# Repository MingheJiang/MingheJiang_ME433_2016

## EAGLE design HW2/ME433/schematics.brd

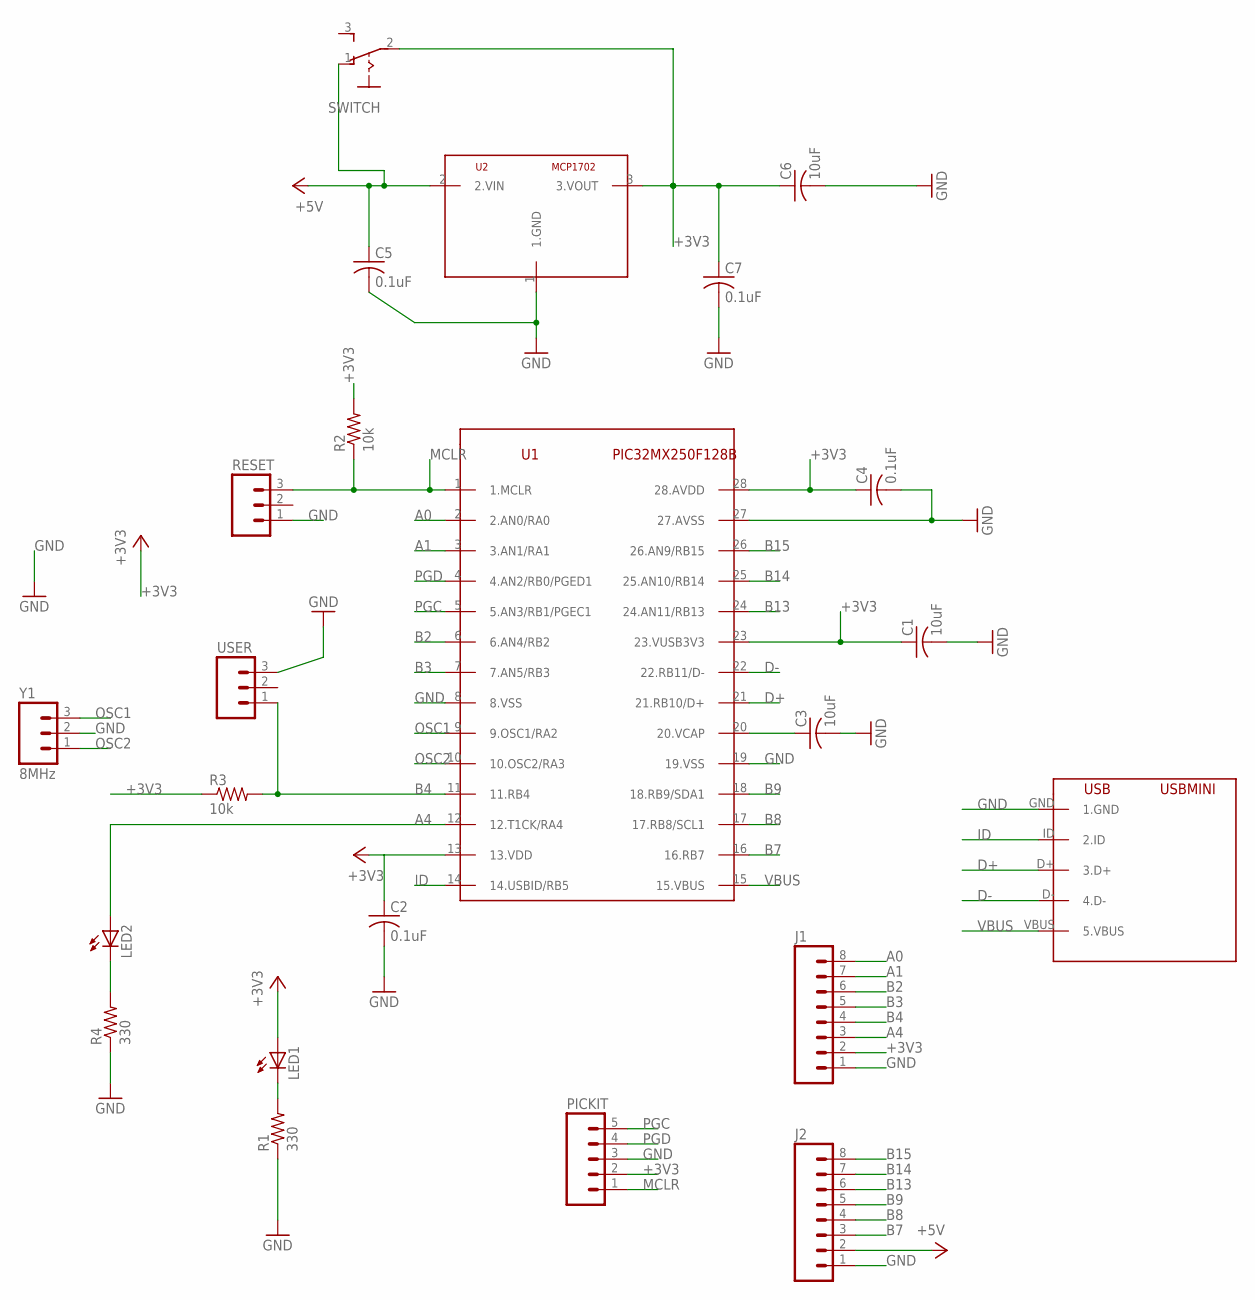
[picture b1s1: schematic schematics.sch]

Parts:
C1, C3, C6: 10uF; C025-024X044
C2, C4, C5, C7: 0.1uF; C025-024X044
J1, J2: M08; 1X08_ROUND
LED1, LED2: LED3MM
PICKIT: M05PTH; 1X05
R1, R4: 330; 0207/10
R2, R3: 10k; 0207/10
RESET: M03PTH; 1X03
SWITCH: 255SB
U1: PIC32MX250F128B; DIL28-3
U2: MCP1702; TO92
USB: USBMINI; USB-MB-H
USER: M03PTH; 1X03
Y1: 8MHz; 1X03

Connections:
+3V3: C1.1, C2.1, C4.1, C6.1, C7.1, J1.2, LED1.A, PICKIT.2, R2.2, R3.1, SWITCH.2, U1.13 (13.VDD), U1.23 (23.VUSB3V3), U1.28 (28.AVDD), U2.3 (3.VOUT)
+5V: C5.1, J2.2, SWITCH.1 (O), U2.2 (2.VIN)
A0: J1.8, U1.2 (2.AN0/RA0)
A1: J1.7, U1.3 (3.AN1/RA1)
A4: J1.3, LED2.A, U1.12 (12.T1CK/RA4)
B2: J1.6, U1.6 (6.AN4/RB2)
B3: J1.5, U1.7 (7.AN5/RB3)
B4: J1.4, R3.2, U1.11 (11.RB4), USER.1
B7: J2.3, U1.16 (16.RB7)
B8: J2.4, U1.17 (17.RB8/SCL1)
B9: J2.5, U1.18 (18.RB9/SDA1)
B13: J2.6, U1.24 (24.AN11/RB13)
B14: J2.7, U1.25 (25.AN10/RB14)
B15: J2.8, U1.26 (26.AN9/RB15)
D+: U1.21 (21.RB10/D+), USB.D+ (3.D+)
D-: U1.22 (22.RB11/D-), USB.D- (4.D-)
GND: C1.2, C2.2, C3.2, C4.2, C5.2, C6.2, C7.2, J1.1, J2.1, PICKIT.3, R1.1, R4.1, RESET.1, U1.8 (8.VSS), U1.19 (19.VSS), U1.27 (27.AVSS), U2.1 (1.GND), USB.GND (1.GND), USER.3, Y1.2
ID: U1.14 (14.USBID/RB5), USB.ID (2.ID)
MCLR: PICKIT.1, R2.1, RESET.3, U1.1 (1.MCLR)
unnamed: LED2.K (C), R4.2
unnamed: LED1.K (C), R1.2
unnamed: C3.1, U1.20 (20.VCAP)
OSC1: U1.9 (9.OSC1/RA2), Y1.3
OSC2: U1.10 (10.OSC2/RA3), Y1.1
PGC: PICKIT.5, U1.5 (5.AN3/RB1/PGEC1)
PGD: PICKIT.4, U1.4 (4.AN2/RB0/PGED1)
VBUS: U1.15 (15.VBUS), USB.VBUS (5.VBUS)

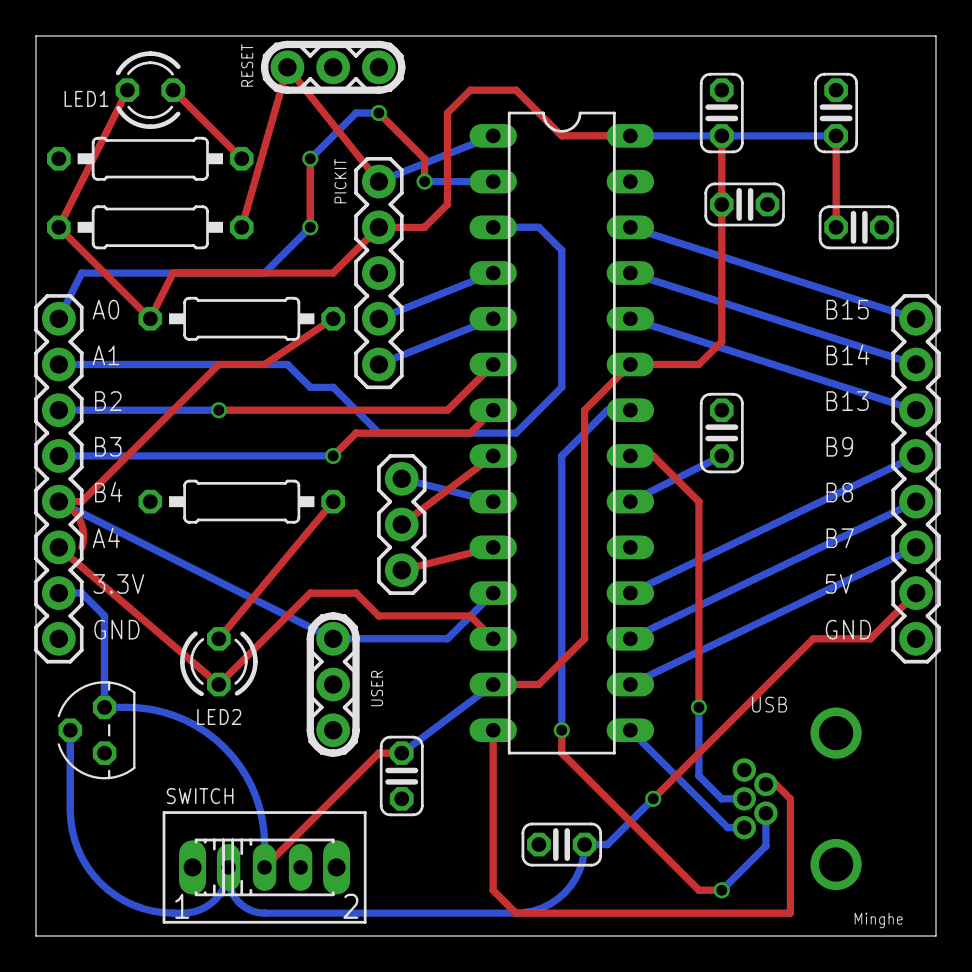
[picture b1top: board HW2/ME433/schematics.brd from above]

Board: 2 copper layers, 50.0 x 50.0 mm, 23 parts (0 on the bottom side), 27 nets.

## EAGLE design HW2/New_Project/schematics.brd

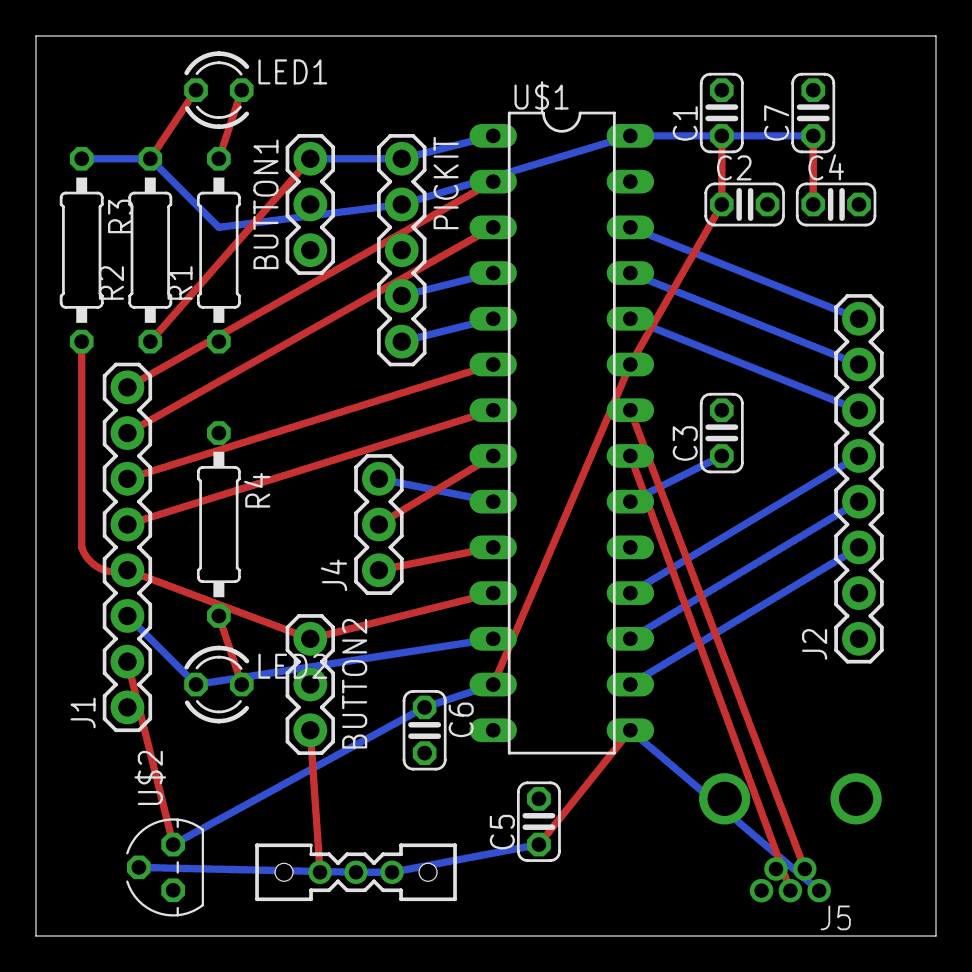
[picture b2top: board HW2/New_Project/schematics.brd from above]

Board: 2 copper layers, 50.0 x 50.0 mm, 23 parts (0 on the bottom side), 25 nets.

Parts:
BUTTON1, BUTTON2: 1X03
C1, C2, C4, C7: 0.1uF; C025-024X044
C3, C6: 10uF; C025-024X044
C5: 1uF; C025-024X044
J1, J2: 1X08_ROUND
J4: 1X03
J5: USB-MB-H
LED1, LED2: LED3MM
PICKIT: 1X05
R1, R4: 330; 0207/10
R2, R3: 10k; 0207/10
U$1: PIC32MX250F128B; DIL28-3
U$2: MCP1702; TO92
U$3: SWITCH

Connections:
+3V3: C1.1, C2.1, C4.1, C6.1, C7.1, J1.2, LED1.A, PICKIT.2, R2.2, R3.1, U$1.13, U$1.23, U$1.28, U$2.3
A0: J1.8, U$1.2
A1: J1.7, U$1.3
A4: J1.3, LED2.A, U$1.12
B2: J1.6, U$1.6
B3: J1.5, U$1.7
B4: BUTTON2.1, J1.4, R3.2, U$1.11
B7: J2.3, U$1.16
B8: J2.4, U$1.17
B9: J2.5, U$1.18
B13: J2.6, U$1.24
B14: J2.7, U$1.25
B15: J2.8, U$1.26
D+: J5.D+, U$1.21
D-: J5.D-, U$1.22
GND: BUTTON1.1, BUTTON2.3, C1.2, C2.2, C3.2, C4.2, C5.2, C6.2, C7.2, J1.1, J2.1, J4.2, J5.GND, PICKIT.3, R1.1, R4.1, U$1.8, U$1.19, U$1.27, U$2.1, U$3.1.GND
MCLR: BUTTON1.3, PICKIT.1, R2.1, U$1.1
unnamed: LED2.K, R4.2
unnamed: LED1.K, R1.2
unnamed: C3.1, U$1.20
OSC1: J4.3, U$1.9
OSC2: J4.1, U$1.10
PGC: PICKIT.5, U$1.5
PGD: PICKIT.4, U$1.4
VBUS: C5.1, J5.VBUS, U$1.15, U$2.2, U$3.2.VIN, U$3.3.VOUT

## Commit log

2016-04-03 photo
2016-04-03 addMPLABX
2016-04-03 template
2016-04-03 modify0
2016-04-03 modify2
2016-04-03 initialization
2016-04-04 addphoto
2016-04-04 markdownfile
2016-04-04 change
2016-04-10 addpic32
2016-04-11 addmost
2016-04-11 addwire
2016-04-11 changewire
2016-04-12 changeusb
2016-04-12 changeposition
2016-04-13 gerber
2016-04-14 Readytobecheckedbeforeorder
2016-04-19 addexpander
2016-04-21 chage
2016-04-22 addled
2016-04-26 checkwhoami
2016-04-26 addpwm
2016-04-28 hw6finished
2016-05-10 addhw5
2016-05-10 addstring
2016-05-10 addpic
2016-05-10 addimupic
2016-05-12 addhw9
2016-05-29 hw12
2016-06-03 modify12
2016-06-04 updatepic
2016-06-04 wheel
2016-06-05 cdcandroid
2016-06-06 changesth
2016-06-09 final
